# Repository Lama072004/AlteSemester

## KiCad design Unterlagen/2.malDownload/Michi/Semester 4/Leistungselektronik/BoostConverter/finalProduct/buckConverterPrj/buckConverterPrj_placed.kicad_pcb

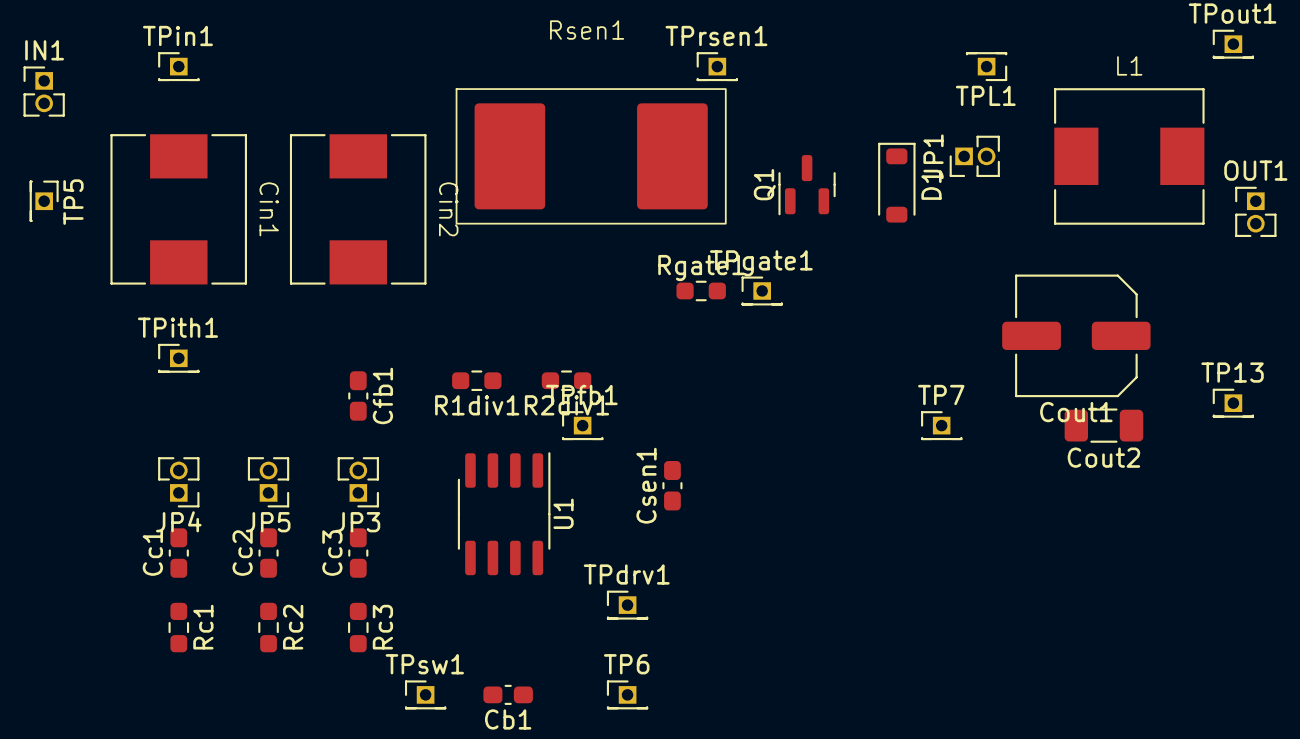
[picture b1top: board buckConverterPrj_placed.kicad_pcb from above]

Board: 2 copper layers, 40 parts (0 on the bottom side), 17 nets, no tracks yet.

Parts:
Cb1: 100n; C_0603_1608Metric_Pad1.08x0.95mm_HandSolder
Cc1: 470p; C_0603_1608Metric_Pad1.08x0.95mm_HandSolder
Cc2: Cc2; C_0603_1608Metric_Pad1.08x0.95mm_HandSolder
Cc3: Cc3; C_0603_1608Metric_Pad1.08x0.95mm_HandSolder
Cfb1: 100p; C_0603_1608Metric_Pad1.08x0.95mm_HandSolder
Cin1: 22u; DR74
Cin2: 220n; DR74
Cout1: 47u; C_Elec_6.3x5.8
Cout2: 100n; C_1206_3216Metric_Pad1.33x1.80mm_HandSolder
Csen1: 100n; C_0603_1608Metric_Pad1.08x0.95mm_HandSolder
D1: DRB070MM-30; D_SOD-123
IN1: Conn_01x02_Pin; PinHeader_1x02_P1.27mm_Vertical
JP1, JP3, JP4, JP5: Jumper_2_Open; PinHeader_1x02_P1.27mm_Vertical
L1: L; DR74
OUT1: Conn_01x02_Pin; PinHeader_1x02_P1.27mm_Vertical
Q1: IRLML0030; SOT-23
R1div1: 10k; R_0603_1608Metric_Pad0.98x0.95mm_HandSolder
R2div1: 62k; R_0603_1608Metric_Pad0.98x0.95mm_HandSolder
Rc1: 22k; R_0603_1608Metric_Pad0.98x0.95mm_HandSolder
Rc2: Rc2; R_0603_1608Metric_Pad0.98x0.95mm_HandSolder
Rc3: Rc3; R_0603_1608Metric_Pad0.98x0.95mm_HandSolder
Rgate1: 10R; R_0603_1608Metric_Pad0.98x0.95mm_HandSolder
Rsen1: 100m; Shunt_4527
TP5, TP6, TP7, TP13: TPgnd; PinHeader_1x01_P1.27mm_Vertical
TPL1: TPL1; PinHeader_1x01_P1.27mm_Vertical
TPdrv1: TPdrv; PinHeader_1x01_P1.27mm_Vertical
TPfb1: TPfb; PinHeader_1x01_P1.27mm_Vertical
TPgate1: TPgate; PinHeader_1x01_P1.27mm_Vertical
TPin1: TPin; PinHeader_1x01_P1.27mm_Vertical
TPith1: TPith; PinHeader_1x01_P1.27mm_Vertical
TPout1: TPout1; PinHeader_1x01_P1.27mm_Vertical
TPrsen1: TPrsen; PinHeader_1x01_P1.27mm_Vertical
TPsw1: TPsw; PinHeader_1x01_P1.27mm_Vertical
U1: LTC1624CS8; SOIC-8_3.9x4.9mm_P1.27mm

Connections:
/drv: Rgate1.1, TPdrv1.1, U1.6 (TG)
/gate: Q1.1 (G), Rgate1.2, TPgate1.1
/ith: JP3.2 (B), JP4.2 (B), JP5.2 (B), TPith1.1, U1.2 (Ith/RUN)
/out: Cout1.1, Cout2.1, L1.2, OUT1.1, R2div1.1, TPout1.1
/sen: Csen1.2, Q1.2 (S), Rsen1.1, TPrsen1.1, U1.1 (ISENSE)
/sw: Cb1.2, D1.1 (K), JP1.1 (A), Q1.3 (D), TPsw1.1, U1.5 (SW)
GND: Cfb1.2, Cin1.2, Cin2.2, Cout1.2, Cout2.2, D1.2 (A), IN1.2, OUT1.2, R1div1.2, Rc1.2, Rc2.2, Rc3.2, TP5.1, TP6.1, TP7.1, TP13.1, U1.4 (GND)
unnamed: Cc1.1, Rc1.1
unnamed: Cc2.1, Rc2.1
unnamed: Cc3.1, Rc3.1
unnamed: JP1.2 (B), L1.1, TPL1.1
unnamed: Cc3.2, JP3.1 (A)
unnamed: Cc1.2, JP4.1 (A)
unnamed: Cc2.2, JP5.1 (A)
unnamed: Cb1.1, U1.7 (BOOST)
unnamed: Cfb1.1, R1div1.1, R2div1.2, TPfb1.1, U1.3 (SET)
VCC: Cin1.1, Cin2.1, Csen1.1, IN1.1, Rsen1.2, TPin1.1, U1.8 (VIN)

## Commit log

2025-10-03 2025-10-3
2026-03-25 27.03.2026
